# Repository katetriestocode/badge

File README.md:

# badge

This is a nfc badge to introduce me! i made it to introduce myself at outpost :))

no firmware since there you can flash the nfc with an app :))

front (it will be white tho!):

back:

pcb:

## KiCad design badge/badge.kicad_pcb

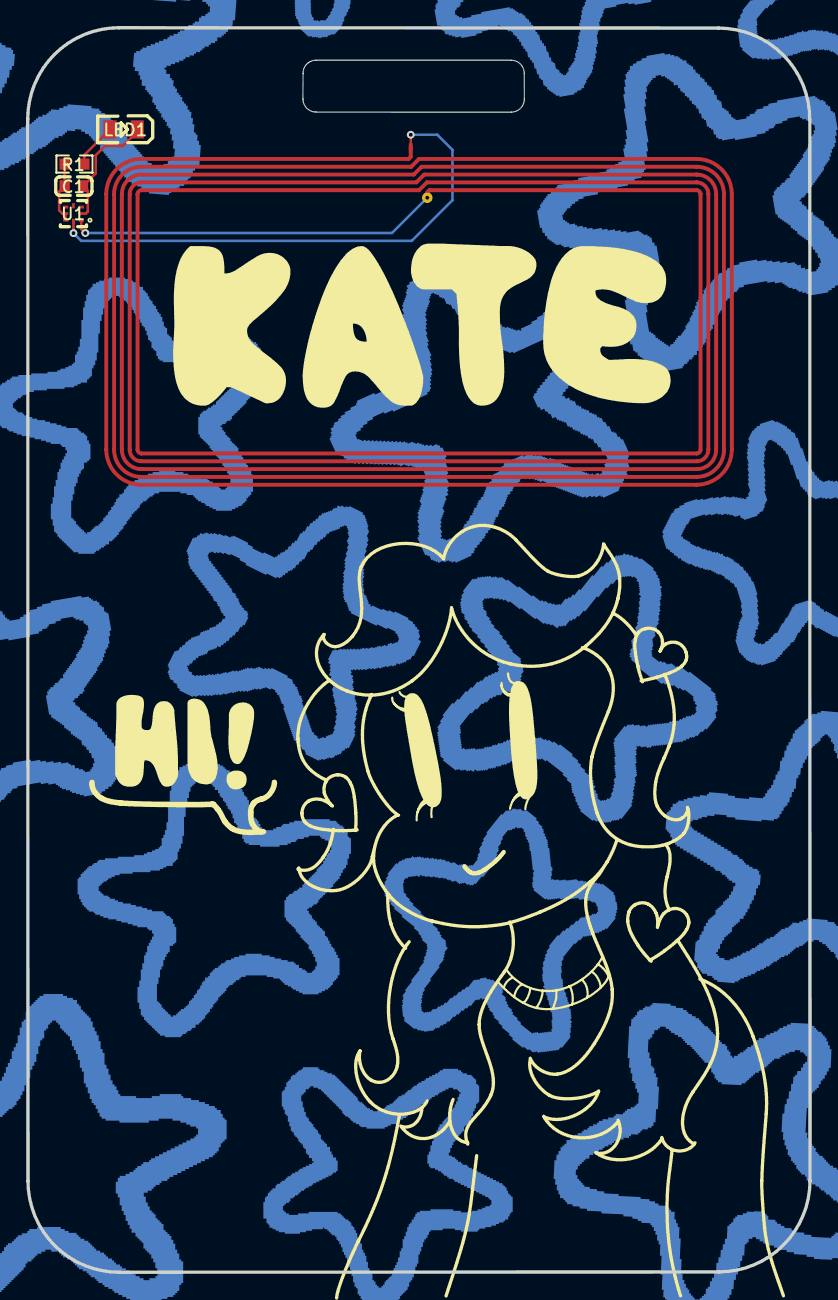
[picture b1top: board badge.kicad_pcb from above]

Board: 2 copper layers, 60.0 x 95.5 mm, 5 parts (0 on the bottom side), 5 nets.

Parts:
2: 25X48MM_NFC_ANTENNA
C1: 220nF; C0603
LED1: 17-21SUYC/TR8; LED0805-R-RD
R1: 47; R0603
U1: NT3H2111W0FHKH; XQFN-8_L1.6-W1.6-P0.50-BL_NT3H2111W0FHKH

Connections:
LED1_1: LED1.1, R1.1
U1_1: 2.P$2, U1.1
U1_2: C1.1, LED1.2, U1.2
U1_6: C1.2, R1.2, U1.6, U1.7
U1_8: 2.P$1, U1.8
